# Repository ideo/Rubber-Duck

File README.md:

# Duck Duck Duck

A companion for Claude Code on Mac. It watches your coding sessions, scores every prompt and response, speaks opinionated reactions, and handles permissions by voice. Optionally connects to a [physical duck](https://duck-duck-duck.edges.ideo.com/) for hardware reactions.

**[Learn more at duck-duck-duck.edges.ideo.com](https://duck-duck-duck.edges.ideo.com/)**

🔒 [**Default intelligence is fully on-device and private**](#data--privacy) on M3+ Macs. M1/M2 users get the best experience with a cloud API key ([free options available](#evaluation)). No cloud audio regardless — your voice never leaves your machine.

## Requirements

- **macOS 26** (Tahoe) or later, **Apple Silicon** (M1 or later)
- **Claude Code** or **Claude Desktop** — [get Claude Code](https://docs.anthropic.com/en/docs/claude-code/overview)

> **On-device scoring is designed for M3+ Apple Silicon.** It works on M1/M2 but runs slowly (~30-60s per eval). For instant reactions on older hardware, add a cloud API key — see [Evaluation](#evaluation) below.

## Install

1. Download `DuckDuckDuck.dmg` from [GitHub Releases](https://github.com/ideo/Rubber-Duck/releases)
2. Drag to Applications, launch
3. Grant **Microphone** and **Speech Recognition** when prompted — all audio stays on-device
4. Accept the **Terms of Use**
5. The app walks you through installing Claude and the plugin
6. Open a Claude Code session (CLI or Desktop) — the duck is watching

<details>
<summary>Build from source</summary>

```bash
git clone https://github.com/ideo/Rubber-Duck.git
cd Rubber-Duck/widget
make run
```

Then use **Setup → Install Plugin** from the menu bar.

Requires Xcode with Swift 6.2+ (macOS 26 SDK).

</details>

## How It Works

```
You  ──►  🦆 Hardware Duck  ──►  Duck Widget (SwiftUI)  ◄──  Claude Code / Desktop
          mic + speaker          eval engine (Foundation      plugin hooks (prompt,
          servo + LED            Models / Haiku / Gemini)     response, permission)
               ▲                        │
               │                   voice out (TTS)
               └────────────────── servo + LED commands
                                   speaker audio

          (no Duck, Duck, Duck device? laptop mic + speakers work too)
```

1. **Hooks** fire on Claude Code events and POST to the widget's embedded server
2. **Eval engine** scores text on-device via Apple Foundation Models (free, sub-second on M3+) — returns scores + a spoken reaction
3. **Widget** animates the duck face, speaks the reaction, optionally drives hardware via USB serial
4. **Voice permissions** — the duck summarizes what Claude wants to do and asks. Say "yes", "always allow", "deny". Foundation Models classifies ambiguous responses.
5. **Voice commands** — say "ducky [command]" to inject text into Claude Code via tmux
6. **Wildcard voice** — score-gated AI picks from 10 voices per reaction (normal, grave, cheerful, dramatic, whisper, etc.)

## Modes

| Mode | What it does | Mic |
|------|-------------|-----|
| **Companion** | Reacts to everything, voice permissions, wake word | On |
| **Permissions Only** | Silent until a permission arrives | On |
| **Companion (No Mic)** | Reacts and speaks, click-only permissions | Off |
| **Relay** (Experimental) | Speak directly to Claude CLI via tmux | On |

## Evaluation

Each prompt and response is scored from -1.0 to +1.0:

| Dimension | What it measures |
|-----------|-----------------|
| **creativity** | Novel/surprising vs boring/obvious |
| **soundness** | Technically solid vs flawed |
| **ambition** | Bold undertaking vs trivial tweak |
| **elegance** | Clean/clear vs hacky/convoluted |
| **risk** | Could break things vs safe |

Defaults to Apple Foundation Models (on-device, free, **designed for M3+**). Switch to Claude Haiku or Gemini Flash from the menu bar for higher-quality scoring. See [Data & Privacy](#data--privacy) for details.

<details>
<summary>M1/M2 Mac? Use a cloud API key for snappy reactions</summary>

On-device scoring runs slowly on M1/M2 (~30-60 seconds per eval). For instant results:

**Gemini Flash (free tier, no credit card):**
1. Go to [aistudio.google.com](https://aistudio.google.com/apikey) and sign in with Google
2. Click Get API Key → Create API Key
3. Paste it into Preferences → Intelligence → Gemini

**Claude Haiku (~$0.001 per eval):**
1. Go to [console.anthropic.com](https://console.anthropic.com/settings/keys) and create an account
2. Add a payment method (pay-as-you-go)
3. Go to API Keys → Create Key
4. Paste it into Preferences → Intelligence → Anthropic

</details>

## Voice

| What you say | What happens |
|---|---|
| "ducky, refactor the auth module" | Command sent to Claude Code |
| "yes" / "no" (during permission) | Approves or denies |
| "always allow" (during permission) | Applies the session-wide suggestion |
| "ducky, quit" | Duck says goodbye |

## Troubleshooting

- **"Claude Code not found"** — [Install Claude Code](https://claude.com/download), then retry the plugin install.
- **No mic permission dialog** — System Settings → Privacy & Security → Microphone → enable Duck Duck Duck.
- **Duck not reacting** — Make sure the widget is running (duck in menu bar) and you have an active Claude session. Try `/reload-plugins`.
- **Duck reacting slowly** — On M1/M2, on-device scoring takes 30-60s per eval. The duck IS working, just thinking. Switch to Gemini or Haiku in Preferences → Intelligence for instant reactions.
- **Plugin not loading** — Start a new session. Hooks are cached at session start.
- **Claude CLI asking for git / Xcode tools** — First-time CLI setup requires Xcode Command Line Tools. Install them when prompted, then run `sudo xcodebuild -license accept` in Terminal to accept the Apple license. Claude won't work until the license is accepted.

## Data & Privacy

By default, Duck Duck Duck's intelligence is **fully contained to your machine**.

| Component | Where it runs | Data sent externally |
|-----------|--------------|---------------------|
| **Apple Foundation Models** (default) | On-device | None. Private and free. Not used for training. |
| **Voice (STT + TTS)** | On-device via Apple APIs | None. No audio leaves your machine. |
| **Claude Haiku eval** (opt-in) | Anthropic API | Prompts/responses sent to Anthropic for scoring. |
| **Gemini Flash eval** (opt-in) | Google API | Prompts/responses sent to Google for scoring. |

In Foundation Models mode (the default), the entire experience — eval scoring, voice recognition, text-to-speech, and the help system — runs privately on your machine at zero cost. [Apple does not use your interactions to train Foundation Models.](https://machinelearning.apple.com/research/introducing-apple-foundation-models)

**M1/M2 note:** On-device scoring is designed for M3+ and runs slowly on older hardware. The app detects this and recommends switching to a cloud provider. If you do, your prompts and responses will be sent externally for scoring (see below). Voice and audio always stay on-device regardless.

**Optional cloud eval:** If you switch to Haiku or Gemini, your prompts and responses are sent directly to the respective API for evaluation. You provide your own API key at your own discretion. Keys are stored locally in `~/Library/Application Support/DuckDuckDuck/` and are never shared. Costs are between you and the API provider. There is no intermediary server — the widget calls the APIs directly.

## Project Structure

```
widget/          SwiftUI macOS app — the duck's brain
plugin/          Claude Code plugin — hooks that connect to the widget
plugin-gemini/   Gemini CLI extension — experimental
firmware/        Arduino firmware for hardware duck (ESP32-S3, Teensy 4.0)
scripts/         Shell scripts (tmux launcher, hook helpers)
hardware/        CAD (SolidWorks, STEP) and EE (Eagle, Fusion 360) source files
bambu/           Bambu Duck — sibling product, see "Other ducks" below
```

## Other ducks in the family

Two distinct products live in this repo. They share lineage (the squelchy
chirp synth, the servo idle behaviors, the same opinionated rubber-duck
voice) but they're built around different hosts:

| | **Claude Code Duck** (this README) | **Bambu Duck** ([`bambu/`](bambu/)) |
|---|---|---|
| **What it watches** | Your Claude Code session on a Mac | A Bambu 3D printer |
| **Host required** | macOS 26 + Claude Code/Desktop | Nothing — runs standalone |
| **Talks via** | Embedded HTTP+WS server on the Mac | ElevenAgents conversational AI |
| **Hardware** | Optional Teensy/ESP32 connected over USB | ESP32-S3 with mic + speaker, WiFi onboard |
| **Setup surface** | App + plugin install on your Mac | Captive portal: WiFi + Bambu login on phone |
| **License/repo** | Same repo, MIT software / CERN-OHL-P-2.0 hardware | Same repo, same licenses |

If you're here for the **Mac/Claude Code duck**, keep reading.

If you're looking for **the 3D-printer companion that needs no computer**: head to [`bambu/`](bambu/) and start with [`bambu/README.md`](bambu/README.md), or skip straight to **[the in-browser flasher](https://ideo.github.io/Rubber-Duck/flash/)** if you already have a duck in hand.

### Hardware (Optional)

Connect the [IDEO Duck, Duck, Duck](https://duck-duck-duck.edges.ideo.com/) or build your own. The widget auto-detects boards via USB. All parts print without supports — pop off the bed and assemble.

- [`hardware/README.md`](hardware/README.md) — enclosure CAD, 3D print settings, assembly instructions, PCB design
- [`firmware/README.md`](firmware/README.md) — supported boards, wiring, flashing, serial protocol

#### Button Controls

The duck has a single button with two modes:

**Normal Mode** (default) — volume control:

| Action | What happens |
|--------|-------------|
| **Press** | Announces current volume level |
| **Press again within 15s** | Cycles to next level: Quack! (75%) → Normal (50%) → Indoor Voice (25%) → Whisper (5%) → Silent (0%) |
| **Hold 2 seconds** | Enter Demo Mode |
| **Hold 5 seconds** | Enter bootloader (for firmware updates) |

Silent mode (0%) mutes all audio — the widget shows subtitles instead. Volume changes on the duck sync to the widget, and vice versa.

**Demo Mode** — show off the duck's personality:

| Action | What happens |
|--------|-------------|
| **Press** | Cycles through 6 emotion presets (Impressed → Excited → Skeptical → Nervous → Disgusted → Bored), each with a unique chirp and spoken quip |
| **Hold 2 seconds** | Exit back to Normal Mode |
| **Hold 5 seconds** | Enter bootloader |
| **30s no button press** | Auto-exits to Normal Mode |

On boot, the duck plays a startup chirp and says "I'm awake." When the widget connects, it says "Connected."

## Development

```bash
cd widget && make run       # release build + launch
cd widget && make sandbox   # re-sign with App Sandbox entitlements
cd widget && make debug     # debug build in terminal
cd widget && make dmg       # notarized DMG for distribution
```

See [`plugin/README.md`](plugin/README.md) for hook details and [`CLAUDE.md`](CLAUDE.md) for architecture notes.

## License

Software (widget, plugin, scripts) — [MIT License](LICENSE)

Hardware (firmware, PCB, enclosure) — [CERN Open Hardware Licence v2 — Permissive](firmware/LICENSE)

## Limitation of Liability

THE ITEM AND THE SOFTWARE ARE PROVIDED AS-IS, AND IDEO MAKES NO WARRANTIES OF ANY KIND, WHETHER EXPRESS, IMPLIED, OR STATUTORY, INCLUDING ANY WARRANTIES OF MERCHANTABILITY, NON-INFRINGEMENT OF INTELLECTUAL PROPERTY RIGHTS, PRODUCT LIFE OR LONGEVITY, OR FITNESS FOR A PARTICULAR PURPOSE, ALL OF WHICH ARE EXPRESSLY DISCLAIMED. USE OF THE ITEM AND THE SOFTWARE IS AT YOUR OWN RISK.

TO THE FULLEST EXTENT ALLOWED UNDER APPLICABLE LAW, IN NO EVENT SHALL IDEO BE LIABLE FOR ANY INCIDENTAL, CONSEQUENTIAL, SPECIAL, OR INDIRECT DAMAGES OF ANY KIND, INCLUDING WITHOUT LIMITATION THOSE RELATING TO LOSS OF USE, LOST PROFITS OR REVENUES, INTERRUPTION OF BUSINESS, AND/OR COST OF PROCUREMENT OF SUBSTITUTE GOODS, REGARDLESS OF (A) THE FORM OF ACTION, WHETHER IN CONTRACT, TORT OR OTHERWISE, (B) WHETHER OR NOT FORESEEABLE, AND (C) EVEN IF ADVISED OF THE POSSIBILITY OF SUCH DAMAGES. IDEO'S AGGREGATE LIABILITY FOR ANY DAMAGES OR LIABILITY CAUSED BY THE ITEM OR THE SOFTWARE SHALL NOT EXCEED $50 IN EACH CASE.

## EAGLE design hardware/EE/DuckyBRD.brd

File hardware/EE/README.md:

# Duck Duck Duck — PCB (EE)

Custom PCB designed in Eagle / Fusion 360 to hold the microcontroller and servo connector inside the duck enclosure.

## Design Files

| File | Description |
|------|-------------|
| `Ducky_Schematic.sch` | Eagle schematic |
| `DuckyBRD.brd` | Eagle board layout |
| `Ducky.f3z` | Fusion 360 project (board + enclosure integration) |

## License

[CERN Open Hardware Licence v2 — Permissive](../../firmware/LICENSE)

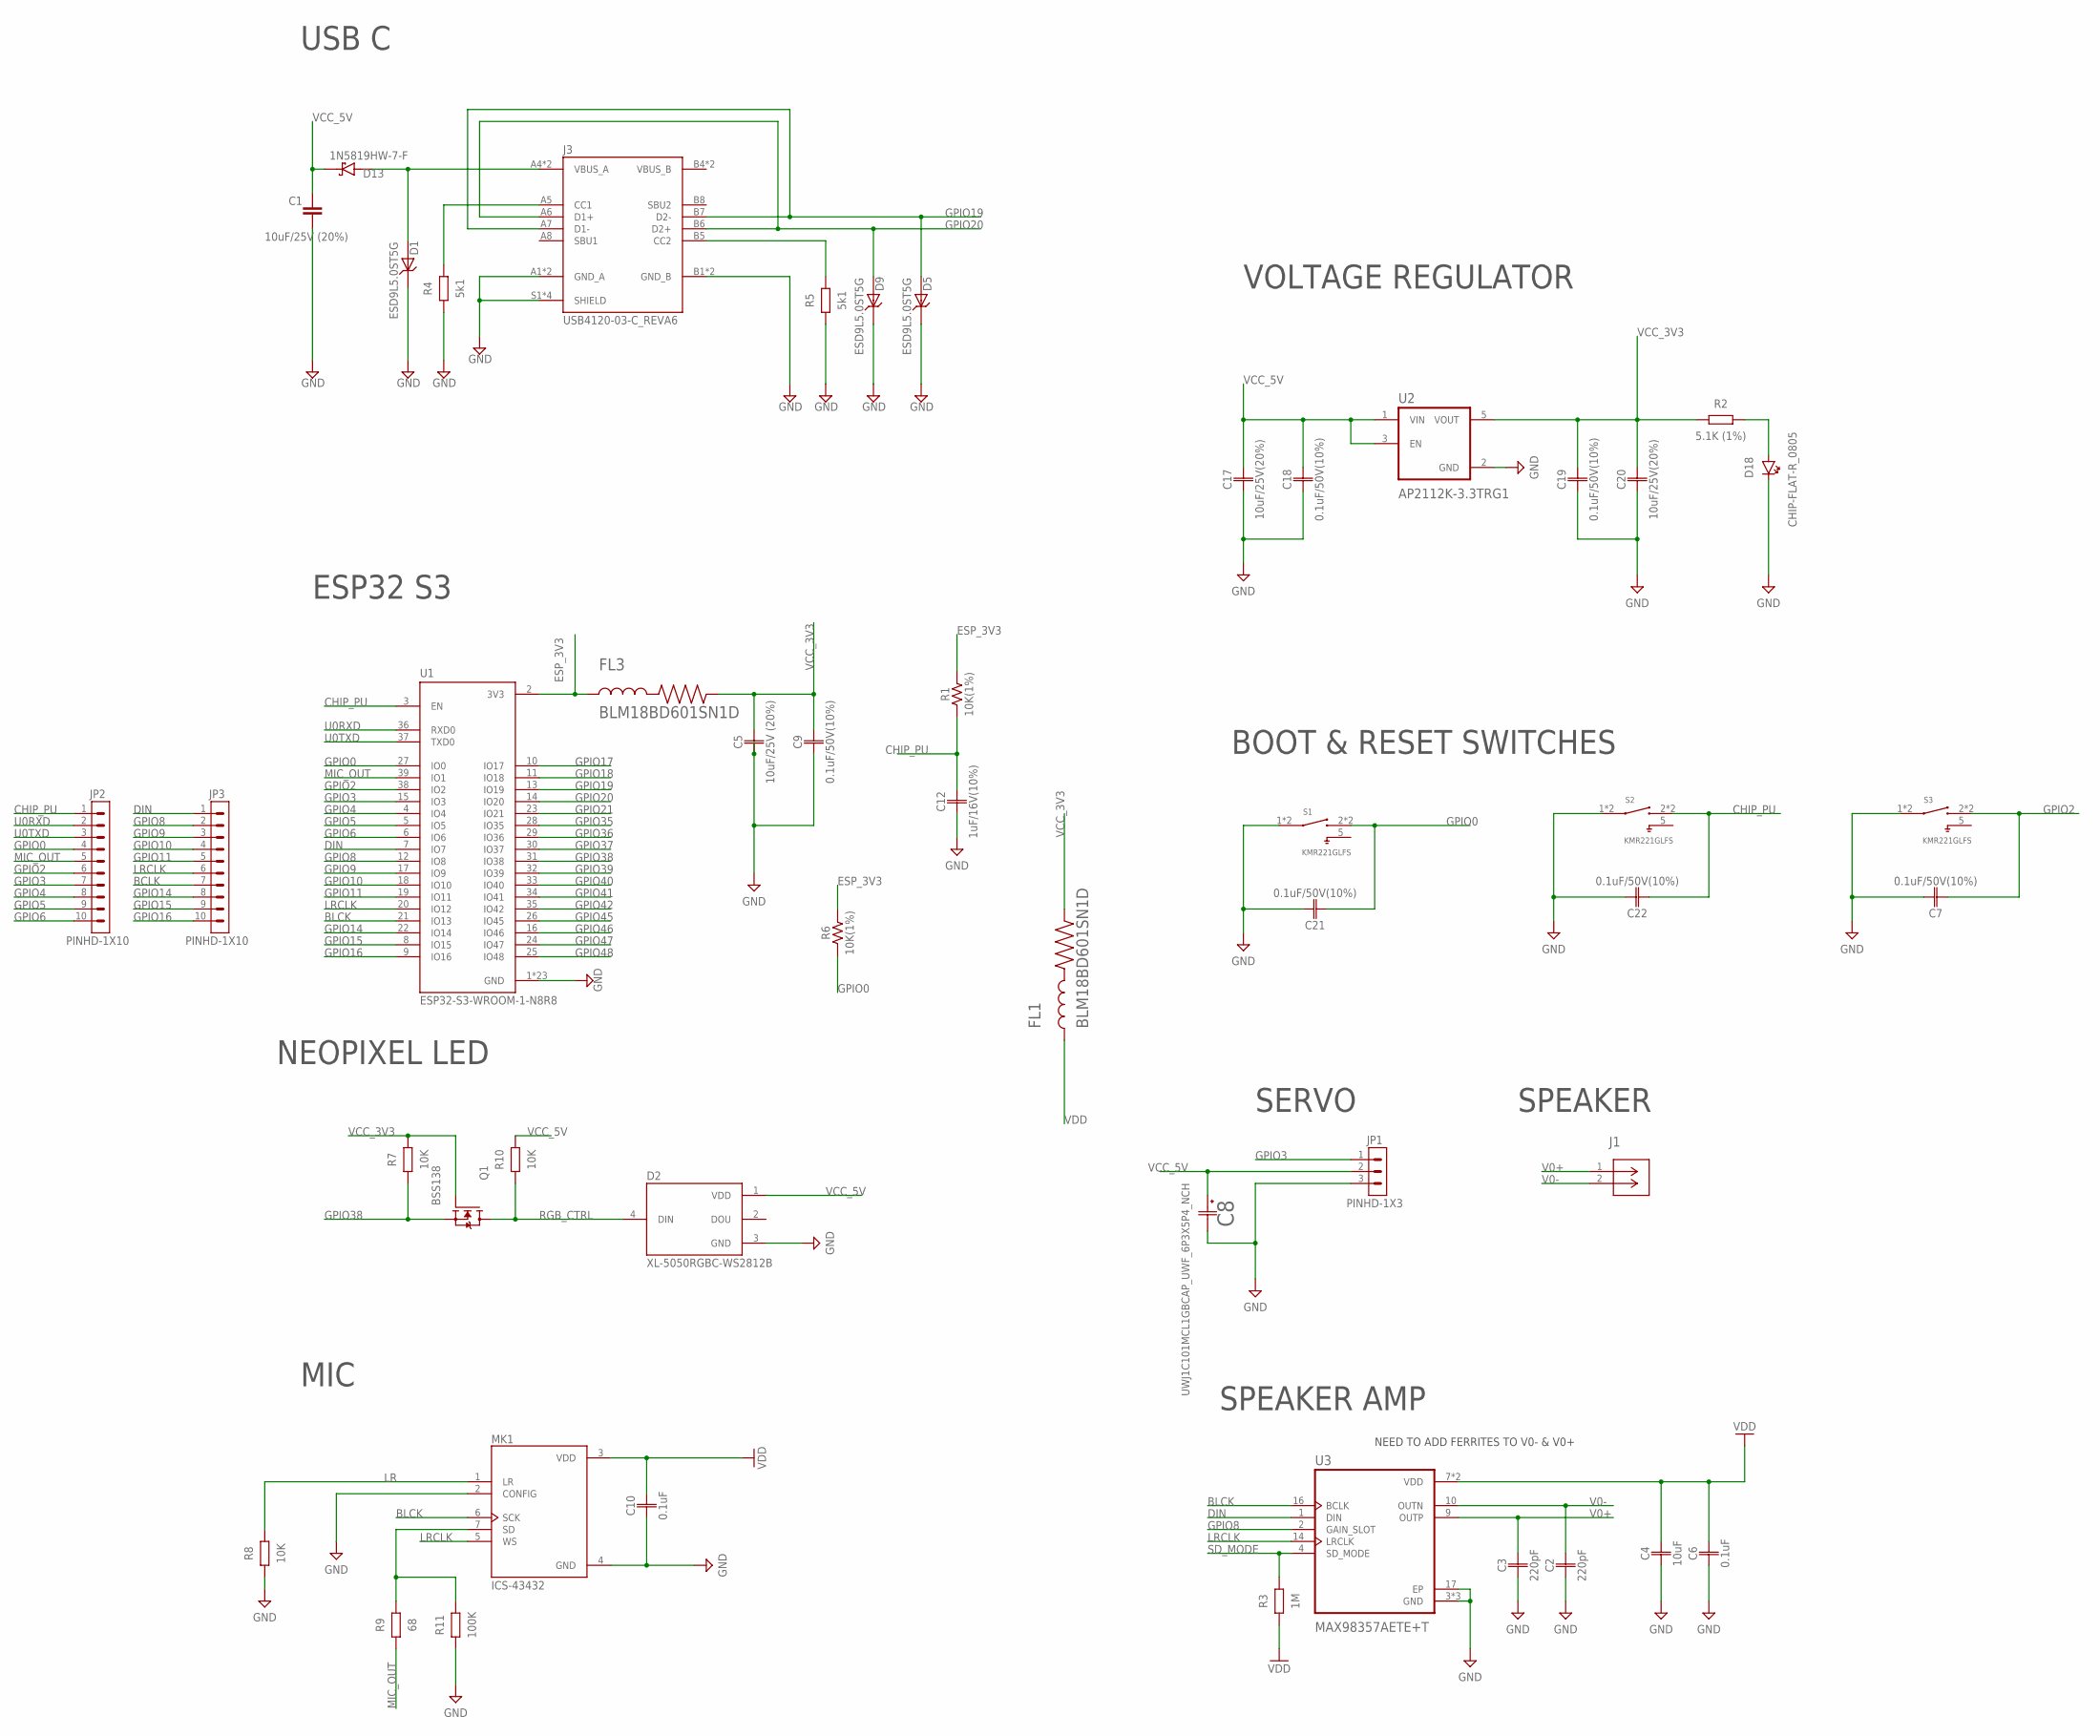
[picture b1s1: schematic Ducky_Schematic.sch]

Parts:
C1, C5: 10uF/25V (20%); CAPC2012X110; LCSC C15850
C2, C3: 220pF; CAPC1608X85; LCSC C27675
C4: 10uF; CAPC1608X85; LCSC C1691
C6, C10: 0.1uF; CAPC1608X85; LCSC C14663
C7, C9, C18, C19, C21, C22: 0.1uF/50V(10%); CAPC2012X110; LCSC C49678
C8: UWJ1C101MCL1GBCAP_UWF_6P3X5P4_NCH; CAP_UWF_6P3X5P4_NCH; LCSC C2887276
C12: 1uF/16V(10%); CAPC2012X110; LCSC C28323
C17, C20: 10uF/25V(20%); CAPC2012X110; LCSC C15850
D1, D5, D9: ESD9L5.0ST5G; DIOM1006X40N; LCSC C82326
D2: XL-5050RGBC-WS2812B; LED_XL-5050RGBC-WS2812B; LCSC C2843785
D13: 1N5819HW-7-F; SOD3715X145N; LCSC C82544
D18: CHIP-FLAT-R_0805; LEDC2012X110N_FLAT-R; LCSC C84256
FL1, FL3: BLM18BD601SN1D; BEADC1608X95N; LCSC C1002
J1: SM02B-SRSS-TBCONN_SM02B-SRSS-TB_JST; CONN_SM02B-SRSS-TB_JST; LCSC C160402
J3: USB4120-03-C_REVA6; GCT_USB4120-03-C_REVA6; LCSC C3445864
JP1: PINHD-1X3; 1X03; LCSC C49257
JP2, JP3: PINHD-1X10; 1X10; LCSC C57369
MK1: ICS-43432; MIC_ICS-43432; LCSC C574021
Q1: BSS138; SOT95P240X111-3N; LCSC C52895
R1, R6: 10K(1%); RESC2012X65; LCSC C17414
R2: 5.1K (1%); RESC2012X65; LCSC C27834
R3: 1M; RESC1608X60; LCSC C22935
R4, R5: 5k1; RESC1608X60; LCSC C23186
R7, R8, R10: 10K; RESC1608X60; LCSC C25804
R9: 68; RESC1608X60; LCSC C23220
R11: 100K; RESC1608X60; LCSC C25803
S1, S2, S3: KMR221GLFS; SW_KMR221GLFS; LCSC C72443
U1: ESP32-S3-WROOM-1-N8R8; XCVR_ESP32S3WROOM1N8R8; LCSC C2913201
U2: AP2112K-3.3TRG1; SOT95P285X140-5N; LCSC C51118
U3: MAX98357AETE+T; QFN50P300X300X80-17N; LCSC C910544

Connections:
BCLK: JP3.7
BLCK: MK1.6 (SCK), U1.21 (IO13), U3.16 (BCLK)
CHIP_PU: C12.2, C22.1, JP2.1, R1.1, S2.2 (3), S2.3, U1.3 (EN)
DIN: JP3.1, U1.7 (IO7), U3.1 (DIN)
ESP_3V3: FL3.1, R1.2, R6.2, U1.2 (3V3)
GND: C1.2, C2.1, C3.1, C4.1, C5.1, C6.1, C7.2, C8.2, C9.1, C10.1, C12.1, C17.1, C18.1, C19.1, C20.1, C21.2, C22.2, D1.C, D2.3 (GND), D9.C, D18.C, J3.A1 (GND_A), J3.A12 (GND_A), J3.B1 (GND_B), J3.B12 (GND_B), J3.S1 (SHIELD), J3.S2 (SHIELD), J3.S3 (SHIELD), J3.S4 (SHIELD), JP1.3, MK1.2 (CONFIG), MK1.4 (GND), R4.1, R5.1, R8.1, R11.1, S1.1, S1.4 (1), S2.1, S2.4 (1), S3.1, S3.4 (1), U1.1 (GND), U1.40 (GND), U1.41_1 (GND), U1.41_2 (GND), U1.41_3 (GND), U1.41_4 (GND), U1.41_5 (GND), U1.41_6 (GND), U1.41_7 (GND), U1.41_8 (GND), U1.41_9 (GND), U1.41_10 (GND), U1.41_11 (GND), U1.41_12 (GND), U1.41_13 (GND), U1.41_14 (GND), U1.41_15 (GND), U1.41_16 (GND), U1.41_17 (GND), U1.41_18 (GND), U1.41_19 (GND), U1.41_20 (GND), U1.41_21 (GND), U2.2 (GND), U3.3 (GND), U3.11 (GND), U3.15 (GND), U3.17 (EP)
GPIO0: C21.1, JP2.4, R6.1, S1.2 (3), S1.3, U1.27 (IO0)
GPIO2: C7.1, JP2.6, S3.2 (3), S3.3, U1.38 (IO2)
GPIO3: JP1.1, JP2.7, U1.15 (IO3)
GPIO4: JP2.8, U1.4 (IO4)
GPIO5: JP2.9, U1.5 (IO5)
GPIO6: JP2.10, U1.6 (IO6)
GPIO8: JP3.2, U1.12 (IO8), U3.2 (GAIN_SLOT)
GPIO9: JP3.3, U1.17 (IO9)
GPIO10: JP3.4, U1.18 (IO10)
GPIO11: JP3.5, U1.19 (IO11)
GPIO14: JP3.8, U1.22 (IO14)
GPIO15: JP3.9, U1.8 (IO15)
GPIO16: JP3.10, U1.9 (IO16)
GPIO17: U1.10 (IO17)
GPIO18: U1.11 (IO18)
GPIO19: D5.A, J3.A7 (D1-), J3.B7 (D2-), U1.13 (IO19)
GPIO20: D9.A, J3.A6 (D1+), J3.B6 (D2+), U1.14 (IO20)
GPIO21: U1.23 (IO21)
GPIO35: U1.28 (IO35)
GPIO36: U1.29 (IO36)
GPIO37: U1.30 (IO37)
GPIO38: Q1.2 (S), R7.1, U1.31 (IO38)
GPIO39: U1.32 (IO39)
GPIO40: U1.33 (IO40)
GPIO41: U1.34 (IO41)
GPIO42: U1.35 (IO42)
GPIO45: U1.26 (IO45)
GPIO46: U1.16 (IO46)
GPIO47: U1.24 (IO47)
GPIO48: U1.25 (IO48)
LR: MK1.1 (LR), R8.2
LRCLK: JP3.6, MK1.5 (WS), U1.20 (IO12), U3.14 (LRCLK)
MIC_OUT: JP2.5, R9.1, U1.39 (IO1)
unnamed: J3.A5 (CC1), R4.2
unnamed: D1.A, D13.A, J3.A4 (VBUS_A), J3.A9 (VBUS_A)
unnamed: J3.B5 (CC2), R5.2
unnamed: MK1.7 (SD), R9.2, R11.2
unnamed: D18.A, R2.2
RGB_CTRL: D2.4 (DIN), Q1.3 (D), R10.1
SD_MODE: R3.2, U3.4 (SD_MODE)
U0RXD: JP2.2, U1.36 (RXD0)
U0TXD: JP2.3, U1.37 (TXD0)
V0+: C3.2, J1.1, U3.9 (OUTP)
V0-: C2.2, J1.2, U3.10 (OUTN)
VBUS_B: J3.B4 (VBUS_B), J3.B9 (VBUS_B)
VCC_3V3: C5.2, C9.2, C19.2, C20.2, FL1.2, FL3.2, Q1.1 (G), R2.1, R7.2, U2.5 (VOUT)
VCC_5V: C1.1, C8.1, C17.2, C18.2, D2.1 (VDD), D13.C (K), JP1.2, R10.2, U2.1 (VIN), U2.3 (EN)
VDD: C4.2, C6.2, C10.2, FL1.1, MK1.3 (VDD), R3.1, U3.7 (VDD), U3.8 (VDD)

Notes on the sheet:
USB C
SERVO
ESP32 S3
NEOPIXEL LED
VOLTAGE REGULATOR
BOOT & RESET SWITCHES
SPEAKER AMP
SPEAKER
NEED TO ADD FERRITES TO V0- & V0+
MIC

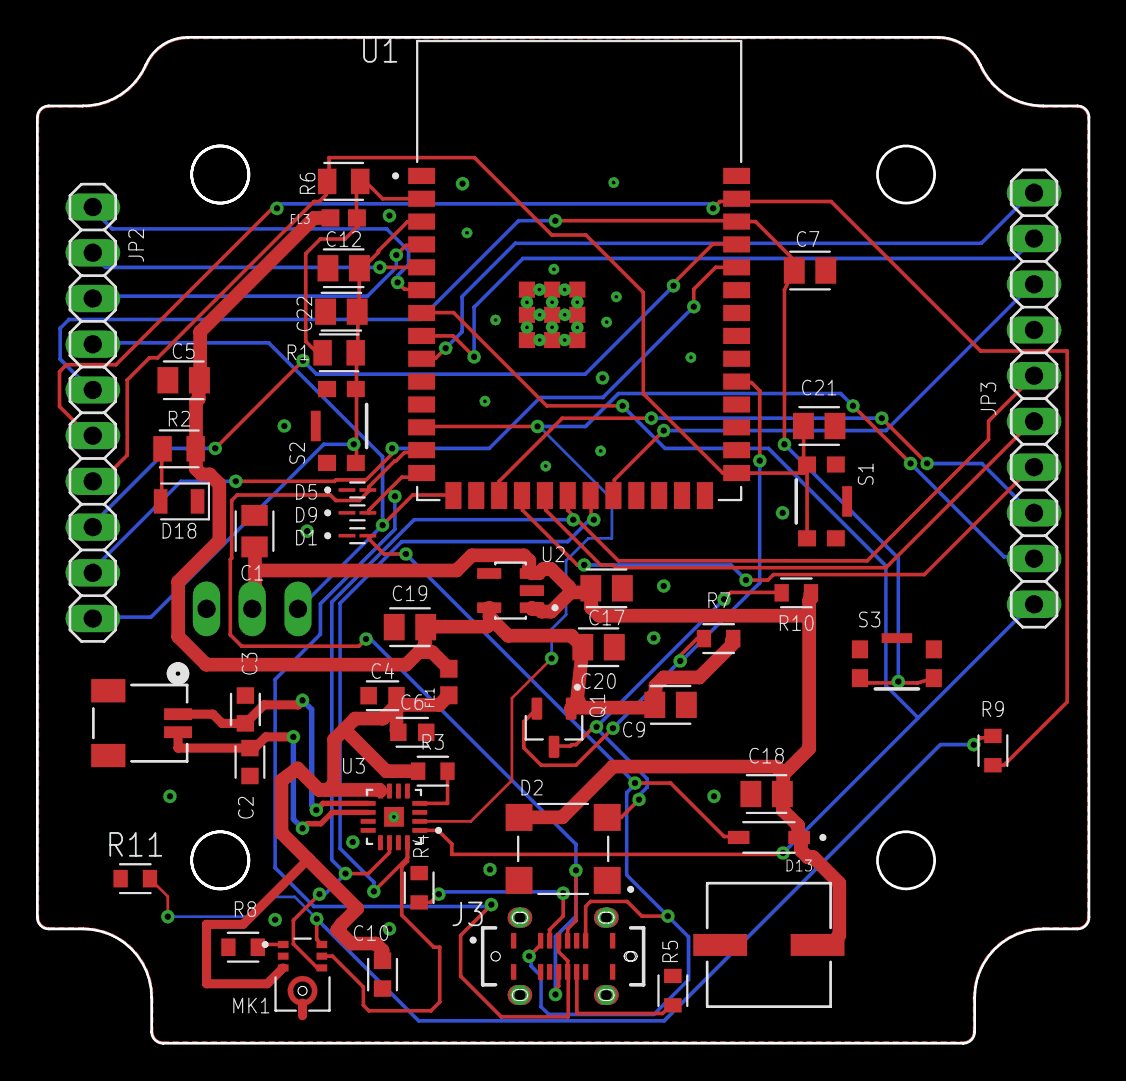
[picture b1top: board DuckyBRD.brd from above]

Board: 2 copper layers, 58.4 x 55.9 mm, 49 parts (1 on the bottom side), 39 nets.

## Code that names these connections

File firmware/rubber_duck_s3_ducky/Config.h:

#ifndef CONFIG_H
#define CONFIG_H

// ============================================================
// RUBBER DUCK S3 DUCKY — Configuration
// ============================================================
// Custom Ducky PCB with ESP32-S3-WROOM-1-N8R8 module.
// On-board: MAX98357 I2S DAC, ICS-43432 I2S mic, WS2812B
// NeoPixel (via BSS138 level shifter), servo header.
//
// CRITICAL: The speaker amp and mic share the same I2S bus
// (BCLK=GPIO13, LRCLK=GPIO12). This firmware uses full-duplex
// I2S on a single port — setupAudio() MUST run before setupMic().
//
// Pin mapping uses raw GPIO numbers (no Dx board macros).
// ============================================================

// --- Feature Toggles ---
#define ENABLE_SERVO       true   // LEDC PWM servo
#define ENABLE_BUTTON      true   // User button (S3 on PCB)
#define ENABLE_AUDIO       true   // I2S speaker output + serial audio streaming
#define ENABLE_MIC         true   // I2S mic capture + serial streaming to widget
#define ENABLE_NEOPIXEL    true   // WS2812B status LED

// --- Mic Type ---
// This board has an ICS-43432 I2S MEMS mic on the shared I2S bus.
// MIC_TYPE 3 = shared full-duplex I2S (RX handle provided by AudioStream).
#define MIC_TYPE           3       // Shared full-duplex I2S mic

// --- Mic Config (shared) ---
#define MIC_SAMPLE_RATE    16000   // Hz — matches STT expectations
#define MIC_FRAME_SAMPLES  256     // Samples per serial frame (16ms at 16kHz)
#define MIC_FRAME_TAG      0x04    // Serial frame type for mic audio

// --- ADC Mic Config (unused on this board, kept for compatibility) ---
#define MIC_PIN            1       // Unused placeholder
#define MIC_DC_OFFSET      2048    // 12-bit ADC midpoint

// --- I2S Mic Config ---
// ICS-43432 shares BCLK/LRCLK with the MAX98357 speaker amp.
// The RX handle is allocated by setupAudio() in full-duplex mode.
// L/R pin pulled LOW via R8 (10K) = left channel output.
#define MIC_I2S_DIN        1       // GPIO1 — mic serial data (MIC_OUT net)

// --- I2S Port Assignment ---
// Single I2S port in full-duplex mode: TX for speaker, RX for mic.
// Both share BCLK (GPIO13) and LRCLK (GPIO12).
#define AUDIO_I2S_PORT     I2S_NUM_0

// --- I2S Pin Config (shared bus) ---
// Speaker amp (MAX98357) and mic (ICS-43432) share clock lines.
//   GPIO13 → BCLK  (to MAX98357 BCLK + ICS-43432 SCK)
//   GPIO12 → LRCLK (to MAX98357 LRCLK + ICS-43432 WS)
//   GPIO7  → DIN   (to MAX98357 DIN — speaker data out)
//   GPIO1  → SD    (from ICS-43432 SD — mic data in)
#define I2S_BCLK_PIN       13      // GPIO13 — shared bit clock
#define I2S_WS_PIN         12      // GPIO12 — shared word select / LRC
#define I2S_DOUT_PIN       7       // GPIO7  — speaker data to MAX98357

// --- MAX98357 GAIN/SLOT Pin ---
// Controls gain and L/R channel selection on the MAX98357.
// Directly connected to ESP32 GPIO8 (no external pull).
//   HIGH  = 15dB gain, left channel
//   LOW   = 12dB gain, right channel
//   Float = 9dB gain, (L+R)/2 mono (default)
#define AMP_GAIN_PIN       8       // GPIO8 — MAX98357 GAIN_SLOT

// --- Audio Config ---
#define AUDIO_SAMPLE_RATE  16000   // Hz — matches widget AVSpeechSynthesizer output
#define AUDIO_BITS         16      // bits per sample
#define AUDIO_CHANNELS     1       // mono (MAX98357 picks L or R based on GAIN pin)

// I2S DMA buffers — these feed the MAX98357 continuously.
#define I2S_DMA_BUF_COUNT  8       // More DMA buffers = more runway before underrun
#define I2S_DMA_BUF_LEN    256     // samples per DMA buffer

// --- Ring Buffer Config ---
#define RING_BUF_SAMPLES   8192
#define RING_BUF_PREFILL   2048

// --- Serial Config ---
#define SERIAL_BAUD        921600

// --- Serial Audio Framing ---
#define FRAME_MODE_AUDIO   0x01
#define FRAME_MODE_CONTROL 0x02
#define FRAME_MAX_BYTES    1200

// --- NeoPixel Config ---
// WS2812B driven through BSS138 MOSFET level shifter on GPIO38.
// BSS138 gate = VCC_3V3, source = GPIO38 + 10K pull-up to 3V3,
// drain = WS2812B DIN + 10K pull-up to 5V.
#define NEOPIXEL_PIN       38      // GPIO38 — WS2812B data (via level shifter)

// --- Servo Config (LEDC PWM) ---
// 3-pin header JP1: GPIO3 = signal, 5V = power, GND
#define SERVO_PIN          3       // GPIO3 — servo signal
#define SERVO_CENTER       90      // Neutral position (degrees)
#define SERVO_RANGE        80      // +/-degrees from center
#define SERVO_MIN          (SERVO_CENTER - SERVO_RANGE)
#define SERVO_MAX          (SERVO_CENTER + SERVO_RANGE)
#define SERVO_UPDATE_MS    20      // Fixed-rate update interval

// --- Button Config ---
// User button S3 on GPIO2 (with debounce cap C7).
// Boot button S1 on GPIO0 is handled by the ROM bootloader.
// Reset button S2 on EN is hardware reset.
#define BUTTON_PIN         2       // GPIO2 — user button (S3 on PCB)
#define LONG_PRESS_MS      2000    // Hold 2s for snap-to-center

// --- Spring Physics (servo) ---
#define SPRING_K           0.06f
#define SPRING_DAMPING     0.82f
#define OSCILLATION_DECAY  0.95f

// --- Expression Timing ---
#define EXPRESSION_HOLD_MS       5000
#define EXPRESSION_RETURN_KICK   0.5f

// --- Idle Heartbeat (servo) ---
#define IDLE_HOP_RANGE     30.0f
#define IDLE_HOP_MIN_MS    4000
#define IDLE_HOP_MAX_MS    15000
#define IDLE_HOP_KICK      0.6f

// --- Idle Cluster (bird-like micro-adjustments) ---
#define IDLE_CLUSTER_DELTA     30.0f
#define IDLE_CLUSTER_MIN_DELTA 10.0f
#define IDLE_CLUSTER_GAP_MIN   500
#define IDLE_CLUSTER_GAP_MAX   1500

// --- Ambient Spring Physics (nag kicks) ---
#define AMBIENT_SPRING_K       0.03f
#define AMBIENT_SPRING_DAMPING 0.88f

// --- Ambient Lerp (idle hops) ---
#define AMBIENT_LERP_RATE      0.25f

// --- TTS Talking Head Animation ---
#define TTS_RETARGET_MS        300
#define TTS_HOP_RANGE          8.0f

// --- Chirp Synthesis ---
#define CHIRP_BASE_FREQ      280
#define CHIRP_DURATION       250
#define CHIRP_AMPLITUDE      0.5f
#define CHIRP_SAMPLE_RATE    16000
#define WHISTLE_SERVO_KICK   15.0f

// --- Permission Nag Servo ---
#define PERMISSION_NAG_MIN     10.0f
#define PERMISSION_NAG_MAX     30.0f
#define PERMISSION_NAG_KICK    1.2f

// --- Permission Nag Config ---
#define PERMISSION_NAG_BASE     6000
#define PERMISSION_NAG_JITTER   2000
#define PERMISSION_BACKOFF_AT   30000
#define PERMISSION_LAZY_BASE    15000
#define PERMISSION_LAZY_JITTER  15000
#define PERMISSION_RARE_AT      120000
#define PERMISSION_RARE_BASE    300000
#define PERMISSION_RARE_JITTER  300000

// ============================================================
// Data Structures
// ============================================================

struct EvalScores {
  float creativity;
  float soundness;
  float ambition;
  float elegance;
  float risk;
  char  source;      // 'U' = user, 'C' = claude
  bool  isValid;
};

struct ServoTarget {
  float angle;
  float oscillationAmp;
};

struct ChirpTarget {
  int   startFreq;
  int   endFreq;
  bool  buzzy;
  float sentiment;
  bool  doubleChirp;
};

// ============================================================
// Extern declarations
// ============================================================

extern EvalScores latestScores;
extern bool       newEvalAvailable;

extern float volumeScale;

// Servo state (ServoControl.ino)
extern bool  calibrationMode;
extern float servoCurrentAngle;
extern float servoTargetAngle;
extern float servoVelocity;
extern float servoOscillationAmp;
extern float servoOscillationPhase;
extern float ambientCurrentOffset;
extern float ambientTargetOffset;
extern float ambientVelocity;
extern bool  ambientSpringActive;
extern unsigned long lastEvalTime;
extern int   demoStep;

// Permission state
extern bool permissionPending;
void enterPermission();
void exitPermission();

// Servo helpers (ServoControl.ino)
void snapToCenter();
void triggerDemoPreset();
void resetAmbient();
void updateDeadLevel();
extern bool deadLevelActive;

// Audio helpers (AudioStream.ino)
void setupAudio();
void audioStreamBegin(uint32_t sampleRate, uint8_t bits, uint8_t channels);
void audioStreamEnd();
void audioStreamWrite(const uint8_t *data, size_t len);
void audioFeedI2S();
bool isAudioStreaming();
void audioChirpBegin();
void audioChirpEnd();

// Chirp helpers (ChirpSynth.ino)
ChirpTarget chirpReducer(EvalScores &scores);
void playChirp(ChirpTarget &target);
void playStartupChirp();
void playPermissionChirp();
void updateChirp();
extern float chirpServoOffset;

// Mic capture (MicCapture.ino)
void setupMic();
void updateMic();
void micSetMuted(bool muted);
extern bool micStreaming;

// NeoPixel status (NeoPixelStatus.ino)
void setupNeoPixel();
void updateNeoPixel();
void neoPixelFlash(uint8_t r, uint8_t g, uint8_t b);

#endif

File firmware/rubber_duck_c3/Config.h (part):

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
// --- ADC Mic Config (MIC_TYPE 0) ---
// SPW2430 analog MEMS mic. DC output biased at ~VDD/2 (1.65V).
// S3: D5=GPIO6=A5. C3: move button to D5, use D1=GPIO3=ADC1_CH3.
#define MIC_PIN            D5      // Analog input pin
#define MIC_DC_OFFSET      2048    // 12-bit ADC midpoint (VDD/2)

// --- I2S Mic Config (MIC_TYPE 2) ---
// Adafruit ICS-43434 I2S MEMS mic. 24-bit, wired to free XIAO pins.
// L/R pin tied to GND = left channel.
#define MIC_I2S_SCK        D9      // GPIO8 — bit clock
#define MIC_I2S_WS         D10     // GPIO9 — word select
#define MIC_I2S_SD         D1      // GPIO2 — serial data in

// --- I2S Port Assignment ---
// S3 has 2 I2S ports. I2S/PDM mic takes I2S_NUM_0, speaker goes on I2S_NUM_1.
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
// --- I2S Pin Config ---
// Board macros D2/D3/D4 resolve correctly on both C3 and S3.
//   S3 Sense: D2=GPIO3, D3=GPIO4, D4=GPIO5
//   C3:       D2=GPIO4, D3=GPIO5, D4=GPIO6
#define I2S_BCLK_PIN       D2
#define I2S_WS_PIN         D3
#define I2S_DOUT_PIN       D4
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
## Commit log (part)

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2026-03-11 Updated widget UI details
2026-03-15 refactor phase 1
2026-03-16 Unyellow
2026-03-16 Minor tweak
2026-03-20 IDEO tag for about
2026-03-30 new queueing system for audio to avoid sound hiccups, fix to always allow, docs on manual improvement
2026-03-30 update checker and improved manual
2026-03-30 subtitles toggle b/c I wanted one
2026-03-31 attempt at filtering
2026-03-31 updates to pass through logic
2026-03-31 reenabling plan mode control
2026-03-31 mic tester
2026-03-31 added hardware files
2026-04-01 media in readme
2026-04-02 readme updates
2026-04-05 Updated printable CAD files and firmware pinouts
2026-04-05 Latest parts
2026-04-05 remove tests
2026-04-05 Renaming
2026-04-06 CAD refactoring
2026-04-07 New pin mappings
2026-04-07 backup mic strategy
2026-04-08 fix for plugin update
2026-04-08 fix for wakeword
2026-04-08 hopefully a fix for install issues for CLI & desktop
2026-04-08 direct installation updating, editing settings.json now
2026-04-08 docs updates
2026-04-08 attempt at checking to see if apple intelligence is enabled
2026-04-09 race condition solve
2026-04-09 hopeful fix for "always" error
2026-04-09 audio debugging
2026-04-09 Revert "audio debugging"
    This reverts commit 2e941453bbefa606e8bf77a969ced9523a326201.
2026-04-09 Revert "race condition solve"
    This reverts commit 9361e3ec6d30c544d0983ea7fd9e87a5e58434de.
2026-04-09 Fixed formatting of manufacture and product names
2026-04-10 auto permissions error, hopeful fix
2026-04-14 Changes made to the firmware to allow for the production PCB firmware
2026-04-15 attempt at permission queue fix
2026-04-15 fix for MCP tool calls that _do_ show up in the UI
2026-04-15 additional part
2026-04-30 Update DIY-back CAD
2026-05-02 Bambu STATE.md: 2026-05-01 milestone — cloud OAuth + SoftAP + tap-to-wake
    Captures yesterday's three flagship features (#37 tap-to-wake, #30
    SoftAP onboarding, #31 cloud OAuth iteration A), the hardening pass
    (atomic tokens.json, /preference auto-resolve, auth_failed surface,
    tap sensitivity polish, printer name in notifications), and what's
    left to make this shippable to a non-developer (#31 iterations B+C).
    Also archives the architectural decisions made during the day —
2026-05-12 Add OpenAI intelligence provider
2026-05-12 Improve firmware USB identification
2026-05-12 Add Codex plugin hooks
2026-06-01 gitignore: ignore SPM build output anywhere (**/.build, **/.swiftpm)
    `boyband/stage/.build/` (and any future Swift package outside `widget/`)
    was being picked up as untracked, cluttering `git status` with hundreds
    of swiftdeps/dia/o files. Generalize the existing `widget/.build/` rule
    to a tree-wide `**/.build/` + `**/.swiftpm/` so any SPM build directory
    gets ignored without needing per-package entries.
    No new packages are committed — this just stops the build chaos.
2026-06-01 gitignore: ignore SPM build output anywhere (**/.build, **/.swiftpm)
    boyband/stage/.build/ (and any future Swift package outside widget/)
    was showing as untracked, cluttering git status with hundreds of
    build artifacts. Generalize the widget/.build/ rule to tree-wide
    **/.build/ + **/.swiftpm/.
    CAD file change included per repo convention (always commit .3mf).
2026-06-01 docs: add bambu/docs/FLASHING.md — single source of truth for flashing
    Flashing procedure has drifted across Claude sessions — scattered
    between bambu/README.md, firmware/README.md (stale, describes the
    pre-captive-portal scaffold), and DEPLOY.md (relay-side only). No one
    place covered the gotchas that have each cost a session.
    New FLASHING.md consolidates all three flash paths and the traps:
    - Web flasher (Chrome/Edge, no toolchain) — the default path
2026-06-01 docs: FLASHING.md — single source of truth for Bambu duck flashing (#56)
    * gitignore: ignore SPM build output anywhere (**/.build, **/.swiftpm)
    boyband/stage/.build/ (and any future Swift package outside widget/)
    was showing as untracked, cluttering git status with hundreds of
    build artifacts. Generalize the widget/.build/ rule to tree-wide
    **/.build/ + **/.swiftpm/.
    CAD file change included per repo convention (always commit .3mf).
2026-06-01 Boy Band: fix websocket audio pacing and socket recovery
2026-06-01 Boy Band: add websocket heartbeat diagnostics
2026-06-01 Boy Band: increase websocket heartbeat cadence
2026-06-01 Boy Band: document websocket heartbeat handoff
2026-06-01 Boy Band: expand full effort handoff
2026-06-01 Boy Band: document secure key handoff
2026-06-02 visualizer, attempt at recovery
2026-06-02 switch to line-by-line playback, not doing great
2026-06-02 functioning usb version! and subtitles view!
2026-06-02 handoff, q&a functioning.... go to http://localhost:3334/show for the experience
2026-06-02 all four! and various fixes
2026-06-02 audio level controls
2026-06-02 fixed q&a input
2026-06-02 tried out q&a history but bailed -- seemed to cause hangs, feels too risky
2026-06-04 q&a with history functioning!
2026-06-04 state dropdown fixes
2026-06-04 visualizer update, pretty mid
2026-06-04 played version at cam studio gathering

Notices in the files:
README.md:
Software License: MIT
Hardware License: CERN-OHL-P-2.0
parts and their libraries:
COPYRIGHT: Copyright (C) 2026 Ultra Librarian. All rights reserved.
